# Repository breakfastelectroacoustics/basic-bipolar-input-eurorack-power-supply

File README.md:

# Basic Bipolar Input Eurorack Power Supply

This power supply derives +12 V, -12 V and +5 V from +12 V AC and -12 V AC with a common GND (as found on a center-tapped 24 V transformer). It is intended as a cheap and simple bipolar (plus 5 V) power supply for modular synthesizers and general test setups.

The double-sided PCB layout is very straightforward. Two AC inputs plus GND coming in on the left and leaving rectified, filtered and regulated on the right.

To keep it as simple as possible the circuit only contains few non-essential components. 7812, 7912 and 7805 linear regulators are used in their basic fixed-voltage configuration (as suggested in the datasheets and used in many designs).

The diodes, voltage regulators and the (bipolar) AC supply used determine the amount of current this power supply can provide. Depending on the application additional fuses or protection diodes are recommended. If heatsinks are used on the linear regulators, they must not touch each other.

Components listed on the BOM are only loosely defined. They have to be specified/adapted to fit individual requirements (with preferably generous safety margins, e.g. capacitors rated 35 V for 12-15 V AC input).

Dimensions: 99.06 x 41.91 mm

Mounting hole pattern: 76.2 x 35.56 mm (~3 mm hole diameter)

The PCB files are licensed under a [Creative Commons Attribution-NonCommercial-ShareAlike 4.0 International License](https://creativecommons.org/licenses/by-nc-sa/4.0/).

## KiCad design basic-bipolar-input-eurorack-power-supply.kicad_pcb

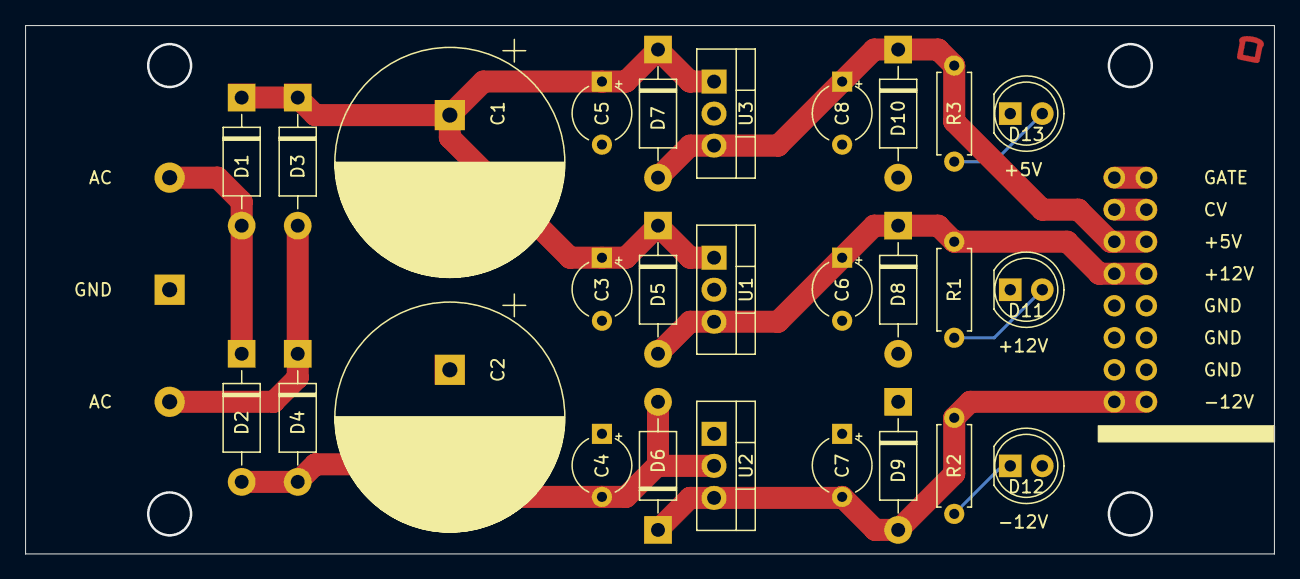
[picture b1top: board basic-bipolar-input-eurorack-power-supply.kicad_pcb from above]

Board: 2 copper layers, 99.1 x 41.9 mm, 27 parts (0 on the bottom side), 11 nets.

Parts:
C1, C2: 4700u; CP_Radial_D18.0mm_P7.50mm
C3, C4, C5, C6, C7, C8: 1u; CP_Radial_Tantal_D4.5mm_P5.00mm
D1, D2, D3, D4, D5, D6, D7, D8, D9, D10: 1N4001; D_DO-41_SOD81_P10.16mm_Horizontal
D11, D12, D13: LED; LED_D5.0mm
R1, R2, R3: R; R_Axial_DIN0207_L6.3mm_D2.5mm_P7.62mm_Horizontal
U1: L7812; TO-220-3_Vertical
U2: L7912; TO-220-3_Vertical
U3: L7805; TO-220-3_Vertical

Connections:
+5V: C8.1, D7.2, D10.1, R3.1, U3.3
+12V: C6.1, D5.2, D8.1, R1.2, U1.3
+12VA: D1.2, D2.1
-12V: C7.2, D6.1, D9.2, R2.2, U2.3
-12VA: D3.2, D4.1
GND: C1.2, C2.1, C3.2, C4.1, C5.2, C6.2, C7.1, C8.2, D8.2, D9.1, D10.2, D11.1, D12.2, D13.1, U1.2, U2.1, U3.2
unnamed: C1.1, C3.1, C5.1, D1.1, D3.1, D5.1, D7.1, U1.1, U3.1
unnamed: C2.2, C4.2, D2.2, D4.2, D6.2, U2.2
unnamed: D11.2, R1.1
unnamed: D12.1, R2.1
unnamed: D13.2, R3.2

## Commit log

2021-05-20 Update BOM
